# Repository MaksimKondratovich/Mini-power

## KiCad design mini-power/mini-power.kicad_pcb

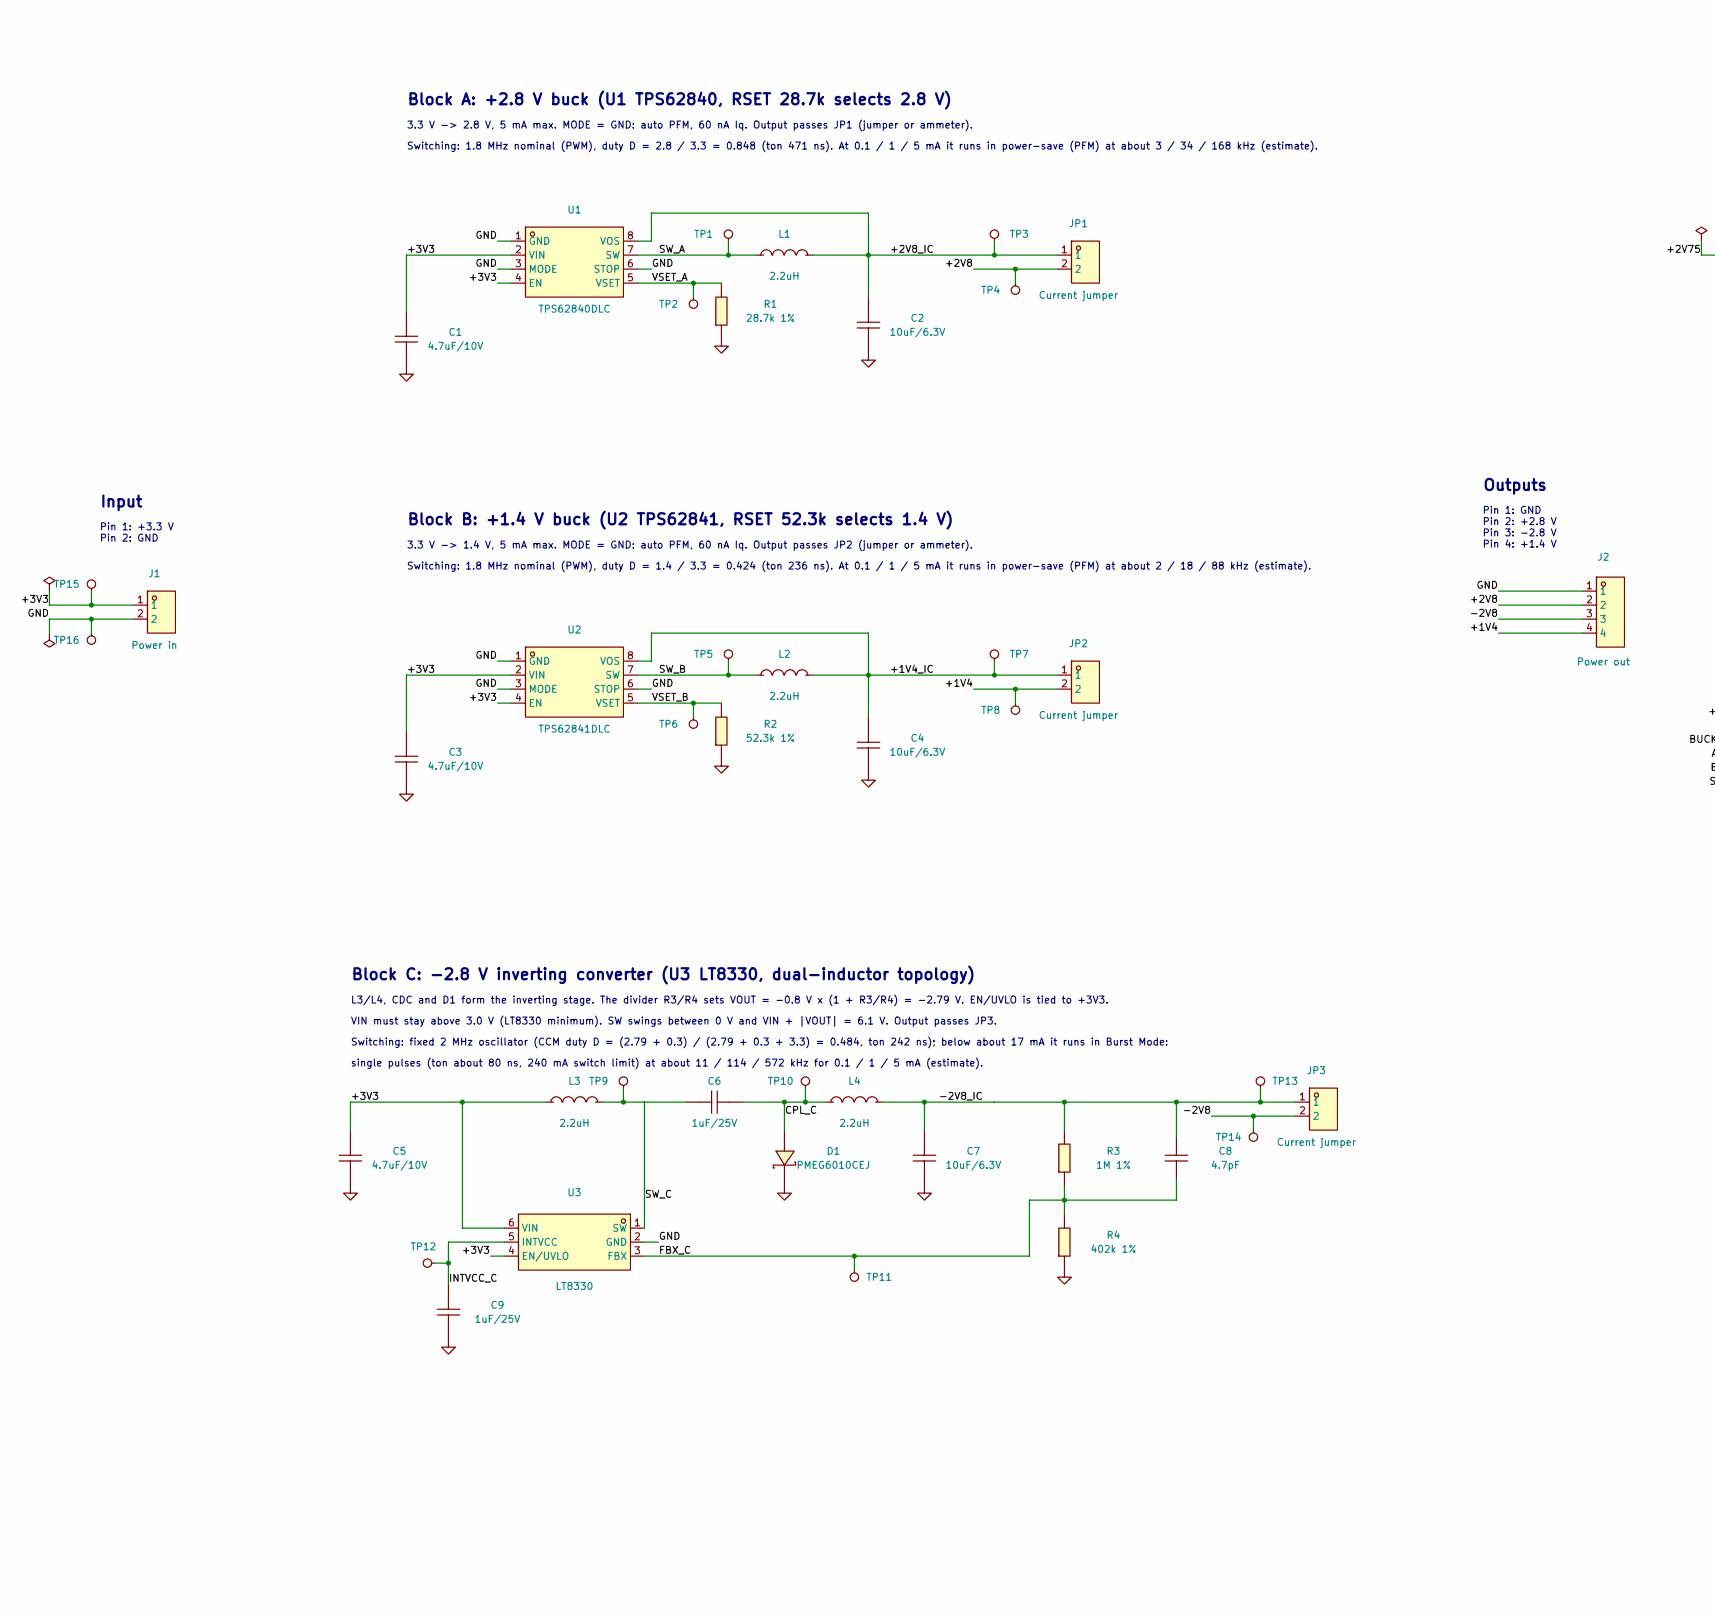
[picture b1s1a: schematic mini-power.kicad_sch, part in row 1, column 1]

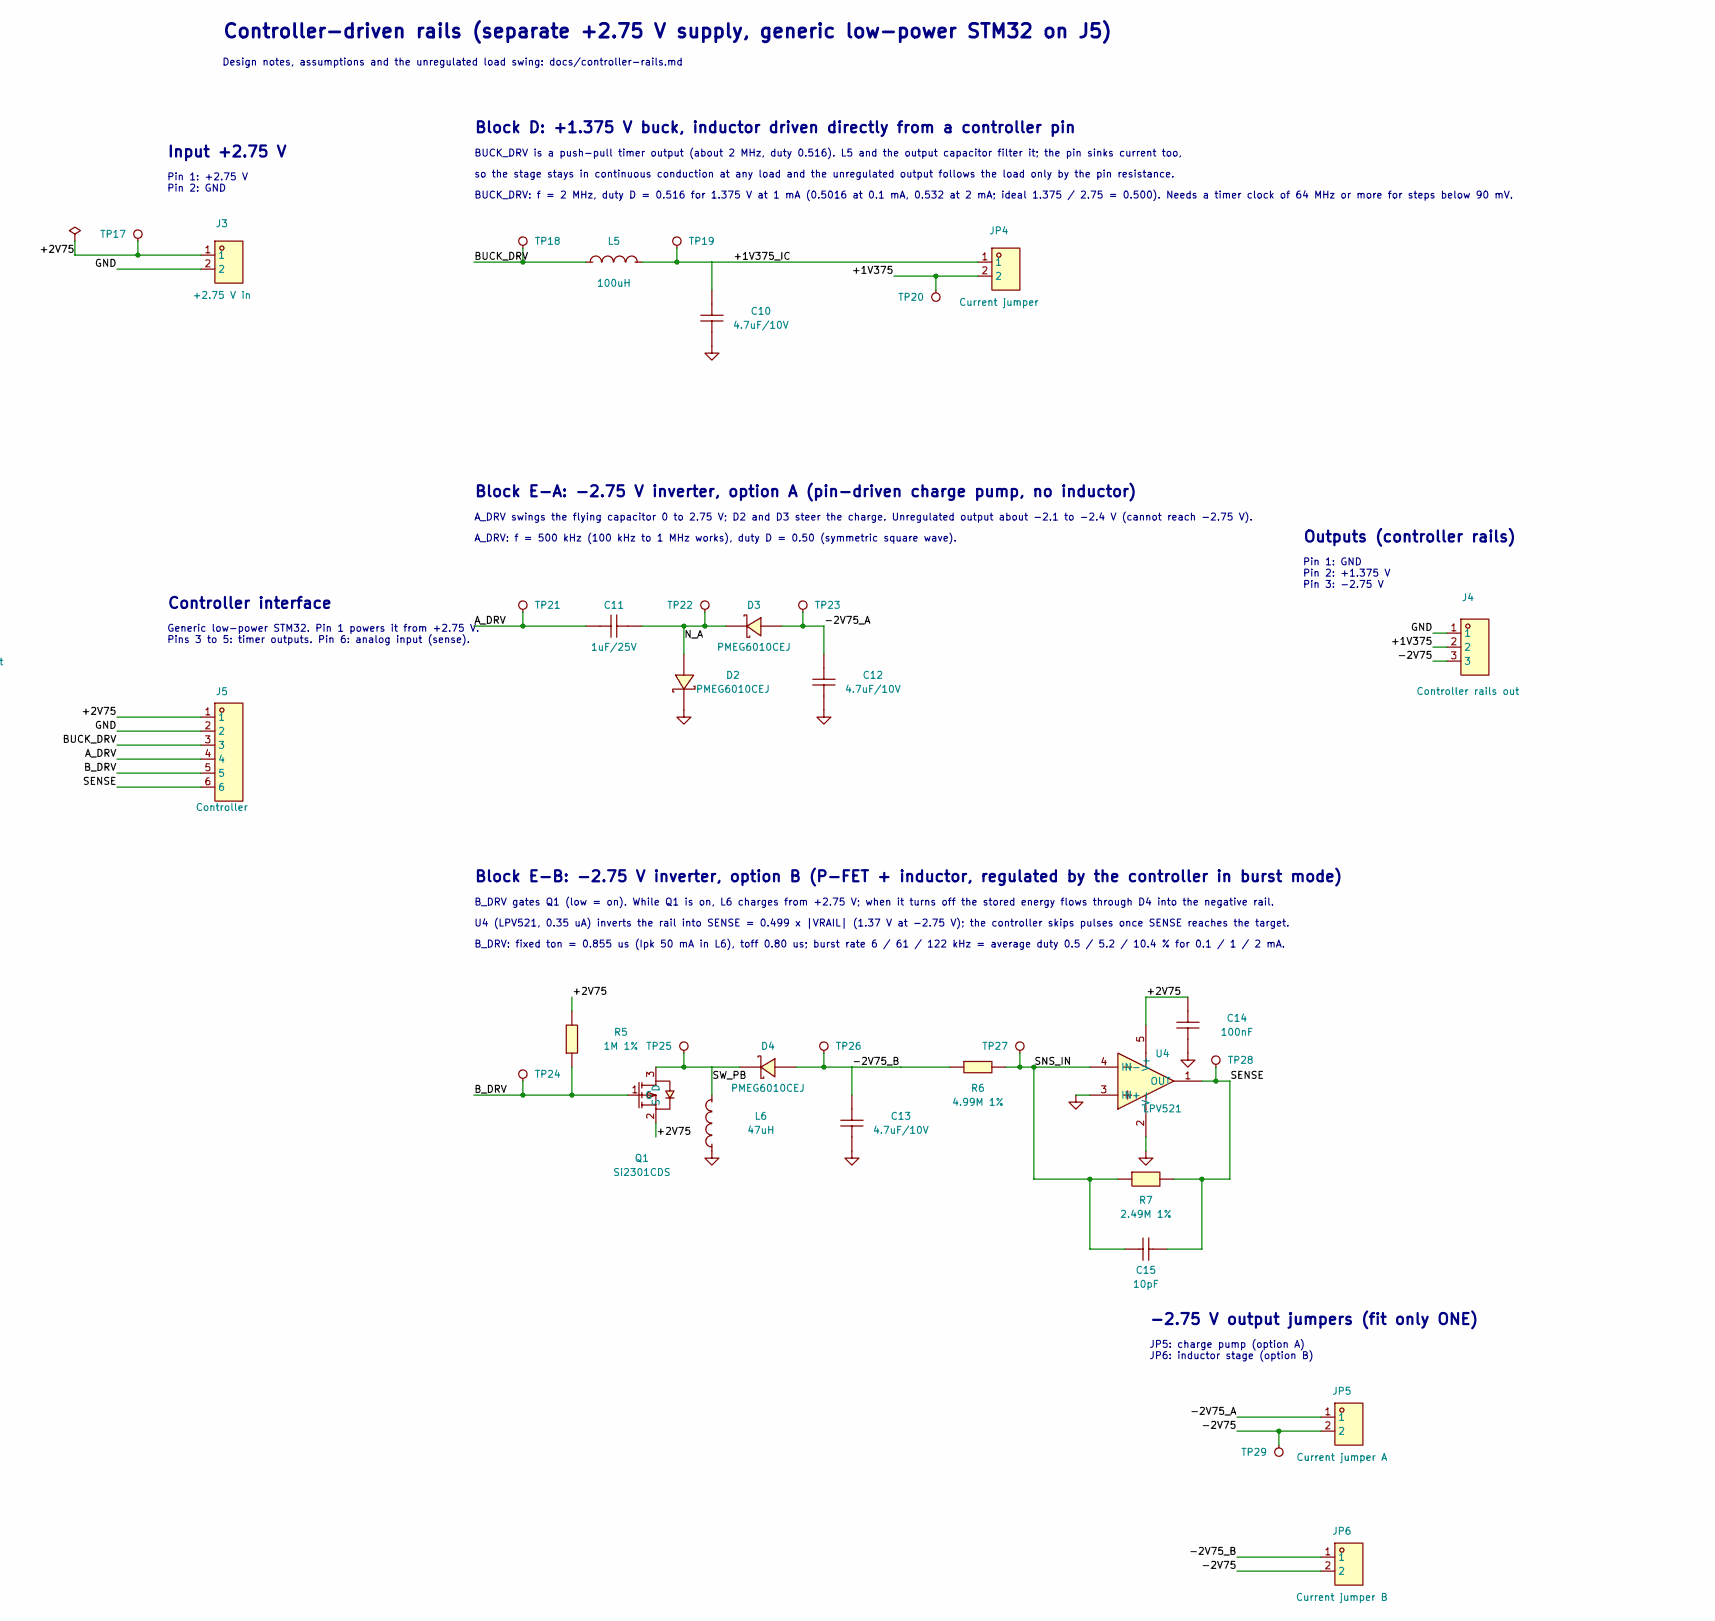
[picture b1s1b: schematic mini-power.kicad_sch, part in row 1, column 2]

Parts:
C1, C3, C5, C10, C12, C13: 4.7uF/10V; C0402; MPN CL05A475MP5NRNC; LCSC Part C23733
C2, C4, C7: 10uF/6.3V; C0402; MPN CGA0402X5R106M6R3GT; LCSC Part C23692971
C6, C9, C11: 1uF/25V; C0402; MPN CL05A105KA5NQNC; LCSC Part C52923
C8: 4.7pF; C0402; MPN 0402CG4R7C500NT; LCSC Part C1569
C14: 100nF; C0402; MPN CL05B104KO5NNNC; LCSC Part C1525
C15: 10pF; C0402; MPN CC0402JRNPO9BN100; LCSC Part C106199
D1, D2, D3, D4: PMEG6010CEJ; SOD-323F_L2.0-W1.6-LS2.5-RD; MPN PMEG6010CEJ,115; LCSC Part C406049
J1: Power in; HDR-TH_2P-P2.54-V-M; MPN PZ254V-11-02P; LCSC Part C492401
J2: Power out; HDR-TH_4P-P2.54-V-M; MPN PZ254V-11-04P; LCSC Part C2691448
J3: +2.75 V in; HDR-TH_2P-P2.54-V-M; MPN PZ254V-11-02P; LCSC Part C492401
J4: Controller rails out; HDR-TH_3P-P2.54-V-M_PZ254V-11-03P; MPN PZ254V-11-03P; LCSC Part C2937625
J5: Controller; HDR-TH_6P-P2.54-V-M; MPN PZ254V-11-06P; LCSC Part C492405
JP1, JP2, JP3, JP4: Current jumper; HDR-TH_2P-P2.54-V-M; MPN PZ254V-11-02P; LCSC Part C492401
JP5: Current jumper A; HDR-TH_2P-P2.54-V-M; MPN PZ254V-11-02P; LCSC Part C492401
JP6: Current jumper B; HDR-TH_2P-P2.54-V-M; MPN PZ254V-11-02P; LCSC Part C492401
L1, L2, L3, L4: 2.2uH; L0806; MPN DFE201612E-2R2M=P2; LCSC Part C337893
L5: 100uH; L0805; MPN LBR2012T101M; LCSC Part C223273
L6: 47uH; L0805; MPN LB2012T470M; LCSC Part C223254
Q1: Si2301CDS; SOT-23-3_L3.0-W1.7-P0.95-LS2.9-BR; MPN SI2301CDS-T1-GE3; LCSC Part C10487
R1: 28.7k 1%; R0402; MPN 0402WGF2872TCE; LCSC Part C26972
R2: 52.3k 1%; R0402; MPN 0402WGF5232TCE; LCSC Part C26982
R3, R5: 1M 1%; R0402; MPN 0402WGF1004TCE; LCSC Part C26083
R4: 402k 1%; R0402; MPN 0402WGF4023TCE; LCSC Part C25785
R6: 4.99M 1%; R0402; MPN RC0402FR-074M99L; LCSC Part C137963
R7: 2.49M 1%; R0402; MPN FRC0402F2494TS; LCSC Part C5159683
TP1: SW_A; TestPoint_0.5mm
TP2: VSET_A; TestPoint_0.5mm
TP3: +2V8_IC; TestPoint_0.5mm
TP4: +2V8; TestPoint_0.5mm
TP5: SW_B; TestPoint_0.5mm
TP6: VSET_B; TestPoint_0.5mm
TP7: +1V4_IC; TestPoint_0.5mm
TP8: +1V4; TestPoint_0.5mm
TP9: SW_C; TestPoint_0.5mm
TP10: CPL_C; TestPoint_0.5mm
TP11: FBX_C; TestPoint_0.5mm
TP12: INTVCC_C; TestPoint_0.5mm
TP13: -2V8_IC; TestPoint_0.5mm
TP14: -2V8; TestPoint_0.5mm
TP15: +3V3; TestPoint_0.5mm
TP16: GND; TestPoint_0.5mm
TP17: +2V75; TestPoint_0.5mm
TP18: BUCK_DRV; TestPoint_0.5mm
TP19: +1V375_IC; TestPoint_0.5mm
TP20: +1V375; TestPoint_0.5mm
TP21: A_DRV; TestPoint_0.5mm
TP22: N_A; TestPoint_0.5mm
TP23: -2V75_A; TestPoint_0.5mm
TP24: B_DRV; TestPoint_0.5mm
TP25: SW_PB; TestPoint_0.5mm
TP26: -2V75_B; TestPoint_0.5mm
TP27: SNS_IN; TestPoint_0.5mm
TP28: SENSE; TestPoint_0.5mm
TP29: -2V75; TestPoint_0.5mm
U1: TPS62840DLC; VSON-8_L2.0-W1.5-P0.50-BL; MPN TPS62840DLCR; LCSC Part C2071859
U2: TPS62841DLC; VSON-8_L2.0-W1.5-P0.50-BL; MPN TPS62841DLCR; LCSC Part C2860681
U3: LT8330; SOT-23-6_L2.9-W1.6-P0.95-LS2.8-BR; MPN LT8330ES6#TRMPBF; LCSC Part C580285
U4: LPV521; SC-70-5_L2.0-W1.3-P0.65-LS2.2-BL; MPN LPV521MGX/NOPB; LCSC Part C779403

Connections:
/+1V4: J2.4, JP2.2, TP8.1
/+1V4_IC: C4.2, JP2.1, L2.2, TP7.1, U2.8 (VOS)
/+1V375: J4.2, JP4.2, TP20.1
/+1V375_IC: C10.2, JP4.1, L5.2, TP19.1
/+2V8: J2.2, JP1.2, TP4.1
/+2V8_IC: C2.2, JP1.1, L1.2, TP3.1, U1.8 (VOS)
/+2V75: C14.2, J3.1, J5.1, Q1.2 (S), R5.2, TP17.1, U4.5 (V+)
/+3V3: C1.2, C3.2, C5.2, J1.1, L3.1, TP15.1, U1.2 (VIN), U1.4 (EN), U2.2 (VIN), U2.4 (EN), U3.4 (EN/UVLO), U3.6 (VIN)
/-2V8: J2.3, JP3.2, TP14.1
/-2V8_IC: C7.2, C8.2, JP3.1, L4.2, R3.2, TP13.1
/-2V75: J4.3, JP5.2, JP6.2, TP29.1
/-2V75_A: C12.2, D3.2 (A), JP5.1, TP23.1
/-2V75_B: C13.2, D4.2 (A), JP6.1, R6.1, TP26.1
/A_DRV: C11.1, J5.4, TP21.1
/BUCK_DRV: J5.3, L5.1, TP18.1
/B_DRV: J5.5, Q1.1 (G), R5.1, TP24.1
/CPL_C: C6.2, D1.2 (A), L4.1, TP10.1
/FBX_C: C8.1, R3.1, R4.2, TP11.1, U3.3 (FBX)
/INTVCC_C: C9.2, TP12.1, U3.5 (INTVCC)
/N_A: C11.2, D2.2 (A), D3.1 (C), TP22.1
/SENSE: C15.2, J5.6, R7.2, TP28.1, U4.1 (OUT)
/SNS_IN: C15.1, R6.2, R7.1, TP27.1, U4.4 (IN-)
/SW_A: L1.1, TP1.1, U1.7 (SW)
/SW_B: L2.1, TP5.1, U2.7 (SW)
/SW_C: C6.1, L3.2, TP9.1, U3.1 (SW)
/SW_PB: D4.1 (C), L6.2, Q1.3 (D), TP25.1
/VSET_A: R1.2, TP2.1, U1.5 (VSET)
/VSET_B: R2.2, TP6.1, U2.5 (VSET)
GND: C1.1, C2.1, C3.1, C4.1, C5.1, C7.1, C9.1, C10.1, C12.1, C13.1, C14.1, D1.1 (C), D2.1 (C), J1.2, J2.1, J3.2, J4.1, J5.2, L6.1, R1.1, R2.1, R4.1, TP16.1, U1.1 (GND), U1.3 (MODE), U1.6 (STOP), U2.1 (GND), U2.3 (MODE), U2.6 (STOP), U3.2 (GND), U4.2 (V-), U4.3 (IN+)

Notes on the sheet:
Block A: +2.8 V buck (U1 TPS62840, RSET 28.7k selects 2.8 V)
3.3 V -> 2.8 V, 5 mA max. MODE = GND: auto PFM, 60 nA Iq. Output passes JP1 (jumper or ammeter).
Switching: 1.8 MHz nominal (PWM), duty D = 2.8 / 3.3 = 0.848 (ton 471 ns). At 0.1 / 1 / 5 mA it runs in power-save (PFM) at about 3 / 34 / 168 kHz (estimate).
Block B: +1.4 V buck (U2 TPS62841, RSET 52.3k selects 1.4 V)
3.3 V -> 1.4 V, 5 mA max. MODE = GND: auto PFM, 60 nA Iq. Output passes JP2 (jumper or ammeter).
Switching: 1.8 MHz nominal (PWM), duty D = 1.4 / 3.3 = 0.424 (ton 236 ns). At 0.1 / 1 / 5 mA it runs in power-save (PFM) at about 2 / 18 / 88 kHz (estimate).
Block C: -2.8 V inverting converter (U3 LT8330, dual-inductor topology)
L3/L4, CDC and D1 form the inverting stage. The divider R3/R4 sets VOUT = -0.8 V x (1 + R3/R4) = -2.79 V. EN/UVLO is tied to +3V3.
VIN must stay above 3.0 V (LT8330 minimum). SW swings between 0 V and VIN + |VOUT| = 6.1 V. Output passes JP3.
Switching: fixed 2 MHz oscillator (CCM duty D = (2.79 + 0.3) / (2.79 + 0.3 + 3.3) = 0.484, ton 242 ns); below about 17 mA it runs in Burst Mode:
single pulses (ton about 80 ns, 240 mA switch limit) at about 11 / 114 / 572 kHz for 0.1 / 1 / 5 mA (estimate).
Input
Pin 1: +3.3 V Pin 2: GND
Outputs
Pin 1: GND Pin 2: +2.8 V Pin 3: -2.8 V Pin 4: +1.4 V
Controller-driven rails (separate +2.75 V supply, generic low-power STM32 on J5)
Design notes, assumptions and the unregulated load swing: docs/controller-rails.md
Input +2.75 V
Pin 1: +2.75 V Pin 2: GND
Controller interface
Generic low-power STM32. Pin 1 powers it from +2.75 V. Pins 3 to 5: timer outputs. Pin 6: analog input (sense).
Block D: +1.375 V buck, inductor driven directly from a controller pin
BUCK_DRV is a push-pull timer output (about 2 MHz, duty 0.516). L5 and the output capacitor filter it; the pin sinks current too,
so the stage stays in continuous conduction at any load and the unregulated output follows the load only by the pin resistance.
BUCK_DRV: f = 2 MHz, duty D = 0.516 for 1.375 V at 1 mA (0.5016 at 0.1 mA, 0.532 at 2 mA; ideal 1.375 / 2.75 = 0.500). Needs a timer clock of 64 MHz or more for steps below 90 mV.
Block E-A: -2.75 V inverter, option A (pin-driven charge pump, no inductor)
A_DRV swings the flying capacitor 0 to 2.75 V; D2 and D3 steer the charge. Unregulated output about -2.1 to -2.4 V (cannot reach -2.75 V).
A_DRV: f = 500 kHz (100 kHz to 1 MHz works), duty D = 0.50 (symmetric square wave).
Block E-B: -2.75 V inverter, option B (P-FET + inductor, regulated by the controller in burst mode)
B_DRV gates Q1 (low = on). While Q1 is on, L6 charges from +2.75 V; when it turns off the stored energy flows through D4 into the negative rail.
U4 (LPV521, 0.35 uA) inverts the rail into SENSE = 0.499 x |VRAIL| (1.37 V at -2.75 V); the controller skips pulses once SENSE reaches the target.
B_DRV: fixed ton = 0.855 us (Ipk 50 mA in L6), toff 0.80 us; burst rate 6 / 61 / 122 kHz = average duty 0.5 / 5.2 / 10.4 % for 0.1 / 1 / 2 mA.
-2.75 V output jumpers (fit only ONE)
JP5: charge pump (option A) JP6: inductor stage (option B)
Outputs (controller rails)
Pin 1: GND Pin 2: +1.375 V Pin 3: -2.75 V

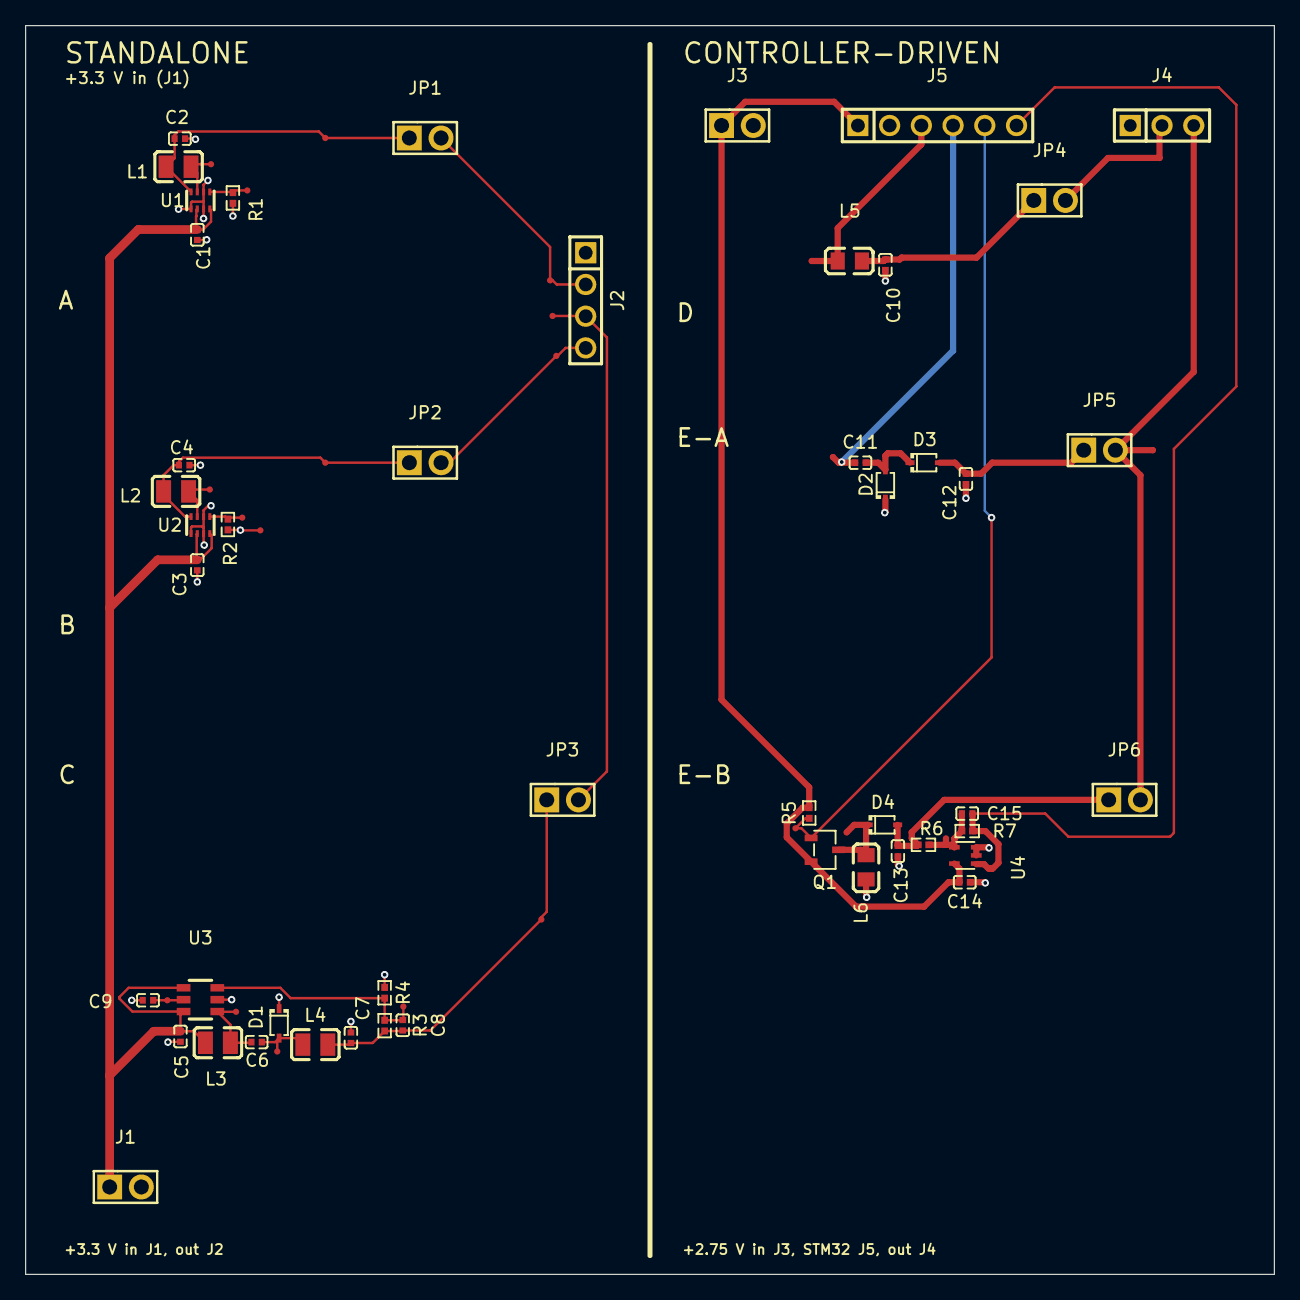
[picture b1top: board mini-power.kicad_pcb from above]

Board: 2 copper layers, 100.0 x 100.0 mm, 77 parts (0 on the bottom side), 29 nets.

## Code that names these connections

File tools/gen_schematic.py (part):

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test_point("SW_C", CX + 8.89, YR, "up", "left")
sw = pins["1"]
s.wire(sw, swn)
s.label("SW_C", (sw[0], sw[1] - 5.08))

# CDC: SW node -> node A
_, cda, cdb = passive_h(C1U, "1uF/25V", CX + 25.4, YR, "C")
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dtop = min(dp.values(), key=lambda q: q[1])
dbot = max(dp.values(), key=lambda q: q[1])
s.wire(anode, dtop)
s.label("CPL_C", (anode[0], YR + 2.54))
gnd_symbol(dbot)

# L4: node A -> output node
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fbx = pins["3"]
vx = CX + 82.55
s.wire(fbx, (CX + 50.8, fbx[1]), (vx, fbx[1]), (vx, fbx_n[1]), fbx_n)
s.label("FBX_C", (fbx[0] + 2.54, fbx[1]))
test_point("FBX_C", CX + 50.8, fbx[1], "down", "right")

# GND pin
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ct2, cb2 = passive_v(C1U, "1uF/25V", ivx, iv[1] + 12.7, "C")
s.wire((ivx, iv[1]), (ivx, iv[1] + 3.81), ct2)
gnd_symbol(cb2)
s.label("INTVCC_C", (ivx, iv[1] + 7.62))
test_point("INTVCC_C", ivx, iv[1] + 3.81, "left", "left")

# output rail to JP3 with TP
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# ---- Block D: +1.375 V buck, inductor driven directly from a pin
yD = 63.5
s.text("Block D: +1.375 V buck, inductor driven directly from a controller pin", (SX, yD - 25.4), size=2.0, bold=True)
s.text("BUCK_DRV is a push-pull timer output (about 2 MHz, duty 0.516). L5 and the output capacitor filter it; the pin sinks current too,",
       (SX, yD - 20.32))
s.text("so the stage stays in continuous conduction at any load and the unregulated output follows the load only by the pin resistance.",
       (SX, yD - 16.51))
s.text("BUCK_DRV: f = 2 MHz, duty D = 0.516 for 1.375 V at 1 mA (0.5016 at 0.1 mA, 0.532 at 2 mA; ideal 1.375 / 2.75 = 0.500). Needs a timer clock of 64 MHz or more for steps below 90 mV.",
       (SX, yD - 12.7))
start = (SX, yD)
s.label("BUCK_DRV", start)
_, l5a, l5b = passive_h(L100, "100uH", SX + 25.4, yD, "L")
s.wire(start, (SX + 8.89, yD), l5a)
test_point("BUCK_DRV", SX + 8.89, yD, "up", "right")
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       (SX, yA - 20.32))
s.text("A_DRV: f = 500 kHz (100 kHz to 1 MHz works), duty D = 0.50 (symmetric square wave).", (SX, yA - 16.51))
start = (SX, yA)
s.label("A_DRV", start)
_, cfa, cfb = passive_h(C1U, "1uF/25V", SX + 25.4, yA, "C")
s.wire(start, (SX + 8.89, yA), cfa)
test_point("A_DRV", SX + 8.89, yA, "up", "right")
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d2a = max(dp2.values(), key=lambda q: q[0])  # anode (pin 2) on the right
s.wire(na, (SX + 41.91, yA), d2c)
test_point("N_A", SX + 41.91, yA, "up", "left")
s.label("N_A", (na[0], yA + 2.54))
noa = (SX + 63.5, yA)
s.wire(d2a, (SX + 59.69, yA), noa)
test_point("-2V75_A", SX + 59.69, yA, "up", "right")
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s.text("B_DRV: fixed ton = 0.855 us (Ipk 50 mA in L6), toff 0.80 us; burst rate 6 / 61 / 122 kHz = average duty 0.5 / 5.2 / 10.4 % for 0.1 / 1 / 2 mA.",
       (SX, yB - 27.94))
start = (SX, yB)
s.label("B_DRV", start)
qx = SX + 31.75
pg = (SX + 17.78, yB)  # gate pull-up junction
q1 = s.place("mp", PFET, "Q1", "Si2301CDS", qx, yB, ref_at=(qx - 1.27, yB + 11.43), val_at=(qx - 1.27, yB + 14.0))
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nsw = (qx + 11.43, ys)
s.wire(q1["3"], (qx + 6.35, ys), nsw)
test_point("SW_PB", qx + 6.35, ys, "up", "left")
s.label("SW_PB", (nsw[0], nsw[1] + 2.54))
lt, lb = passive_v(L47, "47uH", nsw[0], ys + 10.16, "L")
s.wire(nsw, lt)
gnd_symbol(lb)
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inn = (nob[0] + 33.02, ys)
s.wire(rinb, (nob[0] + 30.48, ys), inn)
test_point("SNS_IN", nob[0] + 30.48, ys, "up", "left")
s.label("SNS_IN", inn)
ux, uy = nob[0] + 53.34, ys + 2.54
u4 = nxt("U")
op = s.place("mp", OPA, u4, "LPV521", ux, uy, ref_at=(ux + 3.0, uy - 5.0), val_at=(ux + 3.0, uy + 5.0))
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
